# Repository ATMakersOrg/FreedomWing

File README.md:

# FreedomWing Joystick Adapter

## Overview

The FreedomWing Joystick Adapter provides a way to connect a powerchair joystick to a gaming system. This can enable someone to game with the same joystick they use to control their powerchair. This adapter is compatible with joysticks that attach to the powerchair via a DB9 connector. 

The FreedomWing was designed by [ATMakers](http://atmakers.org/) in collaboration with [The AbleGamers Charity](http://ablegamers.org/) and [GRA-V Robotics](https://www.facebook.com/grav.robotics/). [Makers Making Change](https://makersmakingchange.com/) updated the design of the PCB and created a basic set of documentation for FreedomWing 1.1.

This device is Open Source Hardware. Everything needed to build the device is contained within this repository.

More information is available at http://atmakers.org/featherwing

## License

Software is licensed under the MIT Open Source license.  A copy is provided in the 'software' subdirectory

Hardware designs are licensed under the Creative Commons Attribution Share Alike (CC-BY:SA) license.  A copy is provided in the 'hardware' subdirectory.

Documentation is licensed under the Creative Commons Attribution Share Alike (CC-BY:SA) license.  A copy is provided in the 'documentation' subdirectory.

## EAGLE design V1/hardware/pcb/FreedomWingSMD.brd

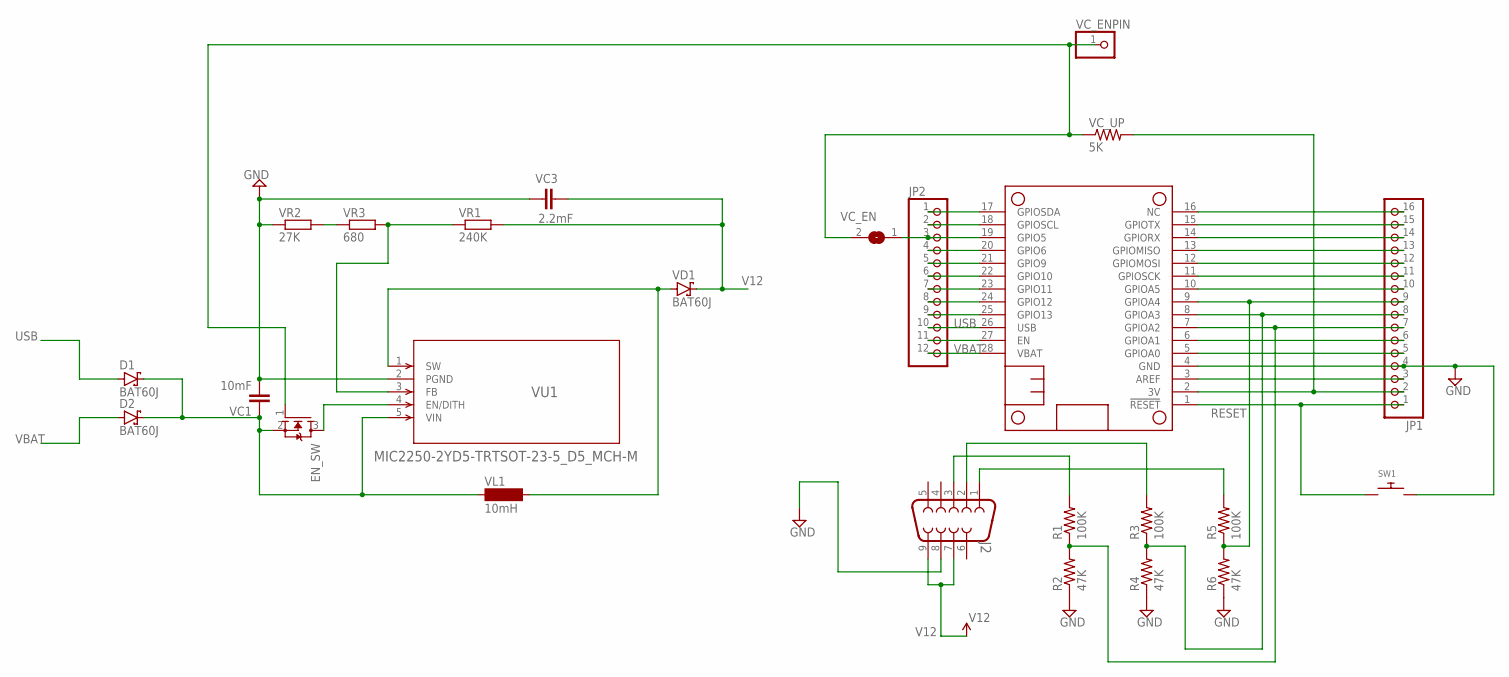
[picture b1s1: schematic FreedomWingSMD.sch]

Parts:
D1, D2: BAT60J; SOD323_ST
EN_SW: MOSFET-NREFLOW; SOT23
J2: DB9MALE; DB9_MALE
JP1: PINHD-1X16; 1X16
JP2: PINHD-1X12; 1X12
MS1: FEATHERWING_NODIM; FEATHERWING_DIM
R1, R3, R5: 100K; R0805
R2, R4, R6: 47K; R0805
SW1: SWITCH_PUSHBUTTONC&K_KSS; BTN_CK_KSS
VC1: 10mF; C0805
VC3: 2.2mF; C0805
VC_EN: SJW
VC_ENPIN: PINHD-1X1; 1X01
VC_UP: 5K; R0805
VD1: BAT60J; SOD323_ST
VL1: 10mH; MS50
VR1: 240K; R0805W
VR2: 27K; R0805W
VR3: 680; R0805W
VU1: MIC2250-2YD5-TRTSOT-23-5_D5_MCH-M; TSOT-23-5_D5_MCH-M

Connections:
3V: JP1.2, MS1.2 (3V), VC_UP.2
GND: J2.8, JP1.4, MS1.4 (GND), R2.1, R4.1, R6.1, SW1.P$2, VC1.2, VC3.1, VR2.1, VU1.2 (PGND)
unnamed: J2.3, R1.2
unnamed: JP2.1, MS1.17 (GPIOSDA)
unnamed: JP2.2, MS1.18 (GPIOSCL)
unnamed: JP2.3, MS1.19 (GPIO5), VC_EN.1
unnamed: JP1.7, MS1.7 (GPIOA2), R1.1, R2.2
unnamed: JP1.8, MS1.8 (GPIOA3), R3.1, R4.2
unnamed: JP1.9, MS1.9 (GPIOA4), R5.1, R6.2
unnamed: VR1.1, VR3.2, VU1.3 (FB)
unnamed: J2.2, R3.2
unnamed: J2.1, R5.2
unnamed: JP2.4, MS1.20 (GPIO6)
unnamed: JP2.5, MS1.21 (GPIO9)
unnamed: JP2.6, MS1.22 (GPIO10)
unnamed: JP2.7, MS1.23 (GPIO11)
unnamed: JP2.8, MS1.24 (GPIO12)
unnamed: JP2.9, MS1.25 (GPIO13)
unnamed: JP1.10, MS1.10 (GPIOA5)
unnamed: JP1.16, MS1.16 (NC)
unnamed: JP1.15, MS1.15 (GPIOTX)
unnamed: JP1.14, MS1.14 (GPIORX)
unnamed: JP1.13, MS1.13 (GPIOMISO)
unnamed: JP1.12, MS1.12 (GPIOMOSI)
unnamed: JP1.11, MS1.11 (GPIOSCK)
unnamed: JP2.11, MS1.27 (EN)
unnamed: EN_SW.3 (D), VU1.4 (EN/DITH)
unnamed: VD1.A, VL1.2, VU1.1 (SW)
unnamed: JP1.3, MS1.3 (AREF)
unnamed: EN_SW.1 (G), VC_EN.2, VC_ENPIN.1, VC_UP.1
unnamed: JP1.6, MS1.6 (GPIOA1)
unnamed: JP1.5, MS1.5 (GPIOA0)
unnamed: VR2.2, VR3.1
RESET: JP1.1, MS1.1 (!RESET), SW1.P$1
USB: D1.A, JP2.10, MS1.26 (USB)
V12: J2.7, J2.9, VC3.2, VD1.C, VR1.2
VBAT: D2.A, JP2.12, MS1.28 (VBAT)
VMAX: D1.C, D2.C, EN_SW.2 (S), VC1.1, VL1.1, VU1.5 (VIN)

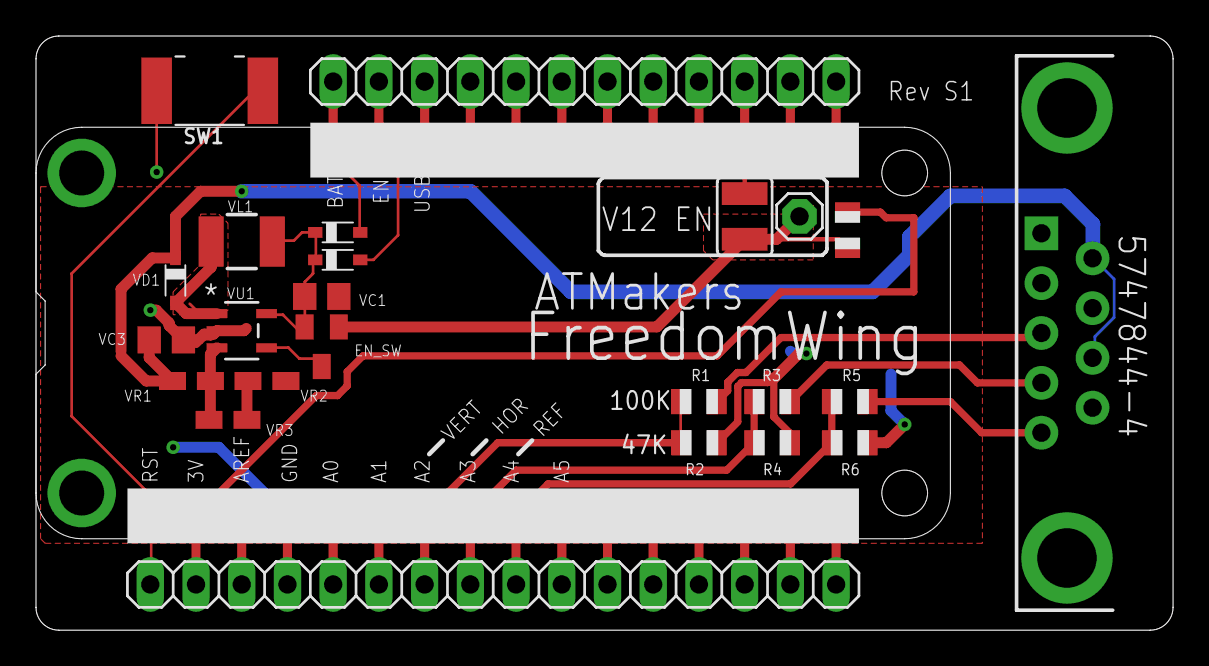
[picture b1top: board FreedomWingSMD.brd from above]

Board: 2 copper layers, 63.2 x 33.0 mm, 25 parts (0 on the bottom side), 38 nets.

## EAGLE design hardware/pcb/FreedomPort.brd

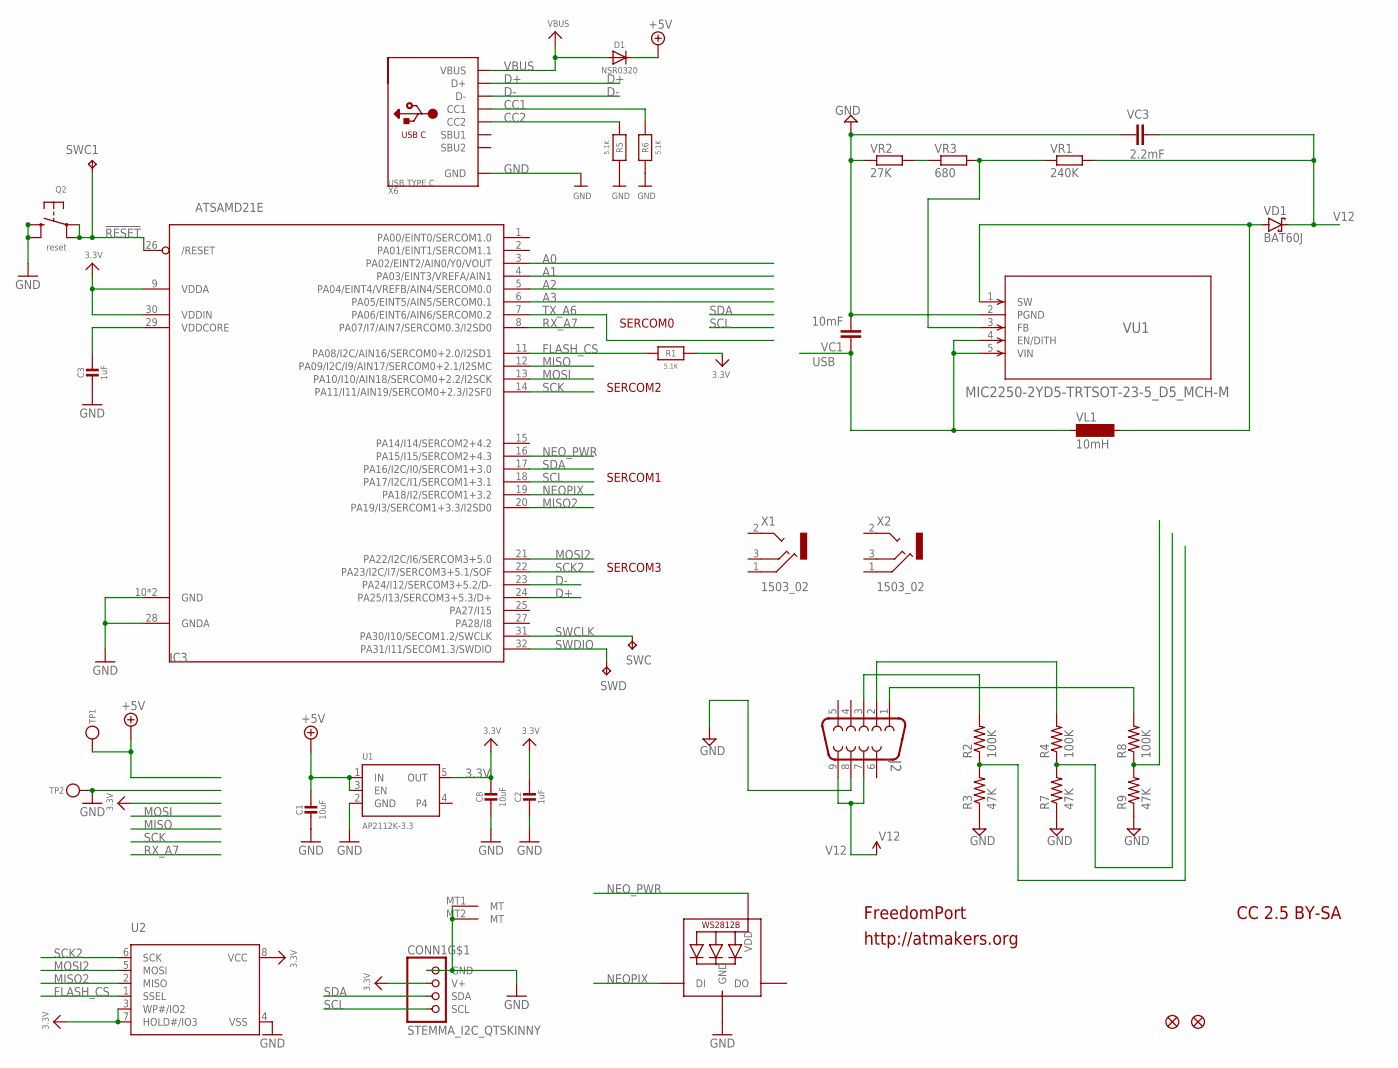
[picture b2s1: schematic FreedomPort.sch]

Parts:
C1, C8: 10uF; _0805MP
C2, C3: 1uF; _0402NO
CONN1: STEMMA_I2C_QTSKINNY; JST_SH4_SKINNY
D1: NSR0320; SOD-323_MINI
IC3: ATSAMD21E; QFN32_5MM
J2: DB9MALE; DB9_MALE
LED1: WS2812B_SK6805_1515; SK6805_1515
Q2: reset; BTN_KMR2_4.6X2.8
R1, R5, R6: 5.1K; _0402NO
R2, R4, R8: 100K; R0805
R3, R7, R9: 47K; R0805
SWC, SWC1: TPB1,27; B1,27
SWD: TPB1,27; B1,27
TP1, TP2: TESTPOINT_1X3; TESTPOINT_RECT_1X3MM
U1: AP2112K-3.3; SOT23-5
U2: SPIFLASH_8PIN; SOIC8_150MIL
U$6, U$8: FIDUCIAL_1MM
VC1: 10mF; C0805
VC3: 2.2mF; C0805
VD1: BAT60J; SOD323_ST
VL1: 10mH; MS50
VR1: 240K; R0805W
VR2: 27K; R0805W
VR3: 680; R0805W
VU1: MIC2250-2YD5-TRTSOT-23-5_D5_MCH-M; TSOT-23-5_D5_MCH-M
X1, X2: 1503_02
X6: USB TYPE C; USB_C_CUSB31-CFM2AX-01-X

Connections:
3.3V: C2.1, C8.1, CONN1.2 (V+), IC3.9 (VDDA), IC3.30 (VDDIN), R1.1, U1.5 (OUT), U2.3 (WP#/IO2), U2.7 (HOLD#/IO3), U2.8 (VCC)
!RESET: IC3.26 (/RESET), Q2.A, Q2.A' (P1), SWC1.TP
+5V: C1.1, D1.C, TP1.P$1, U1.1 (IN), U1.3 (EN)
A0: IC3.3 (PA02/EINT2/AIN0/Y0/VOUT)
A1: IC3.4 (PA03/EINT3/VREFA/AIN1)
A2: IC3.5 (PA04/EINT4/VREFB/AIN4/SERCOM0.0)
A3: IC3.6 (PA05/EINT5/AIN5/SERCOM0.1)
CC1: R6.2, X6.A5 (CC1)
CC2: R5.2, X6.B5 (CC2)
D+: IC3.24 (PA25/I13/SERCOM3+5.3/D+), X6.A6 (D+), X6.B6 (D+)
D-: IC3.23 (PA24/I12/SERCOM3+5.2/D-), X6.A7 (D-), X6.B7 (D-)
FLASH_CS: IC3.11 (PA08/I2C/AIN16/SERCOM0+2.0/I2SD1), R1.2, U2.1 (SSEL)
GND: C1.2, C2.2, C3.2, C8.2, CONN1.1 (GND), CONN1.MT1 (MT), CONN1.MT2 (MT), IC3.10 (GND), IC3.28 (GNDA), IC3.33 (GND), J2.8, LED1.4 (GND), Q2.B (S), Q2.B' (S1), R3.1, R5.1, R6.1, R7.1, R9.1, TP2.P$1, U1.2 (GND), U2.4 (VSS), VC1.2, VC3.1, VR2.1, VU1.2 (PGND), X6.A1B12 (GND), X6.B1A12 (GND)
MISO: IC3.12 (PA09/I2C/I9/AIN17/SERCOM0+2.1/I2SMC)
MISO2: IC3.20 (PA19/I3/SERCOM1+3.3/I2SD0), U2.2 (MISO)
MOSI: IC3.13 (PA10/I10/AIN18/SERCOM0+2.2/I2SCK)
MOSI2: IC3.21 (PA22/I2C/I6/SERCOM3+5.0), U2.5 (MOSI)
unnamed: J2.3, R2.2
unnamed: R2.1, R3.2
unnamed: R4.1, R7.2
unnamed: R8.1, R9.2
unnamed: VR1.1, VR3.2, VU1.3 (FB)
unnamed: J2.2, R4.2
unnamed: J2.1, R8.2
unnamed: VD1.A, VL1.2, VU1.1 (SW)
unnamed: VR2.2, VR3.1
NEOPIX: IC3.19 (PA18/I2/SERCOM1+3.2), LED1.1 (DI)
NEO_PWR: IC3.16 (PA15/I15/SERCOM2+4.3), LED1.2 (VDD)
RX_A7: IC3.8 (PA07/I7/AIN7/SERCOM0.3/I2SD0)
SCK: IC3.14 (PA11/I11/AIN19/SERCOM0+2.3/I2SF0)
SCK2: IC3.22 (PA23/I2C/I7/SERCOM3+5.1/SOF), U2.6 (SCK)
SCL: CONN1.4 (SCL), IC3.18 (PA17/I2C/I1/SERCOM1+3.1)
SDA: CONN1.3 (SDA), IC3.17 (PA16/I2C/I0/SERCOM1+3.0)
SWCLK: IC3.31 (PA30/I10/SECOM1.2/SWCLK), SWC.TP
SWDIO: IC3.32 (PA31/I11/SECOM1.3/SWDIO), SWD.TP
TX_A6: IC3.7 (PA06/EINT6/AIN6/SERCOM0.2)
USB: VC1.1, VL1.1, VU1.4 (EN/DITH), VU1.5 (VIN)
V12: J2.7, J2.9, VC3.2, VD1.C, VR1.2
VBUS: D1.A, X6.A4B9 (VBUS), X6.B4A9 (VBUS)
VDDCORE: C3.1, IC3.29 (VDDCORE)

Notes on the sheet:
FreedomPort
http://atmakers.org
CC 2.5 BY-SA
SERCOM0
SERCOM1
SERCOM2
SERCOM3

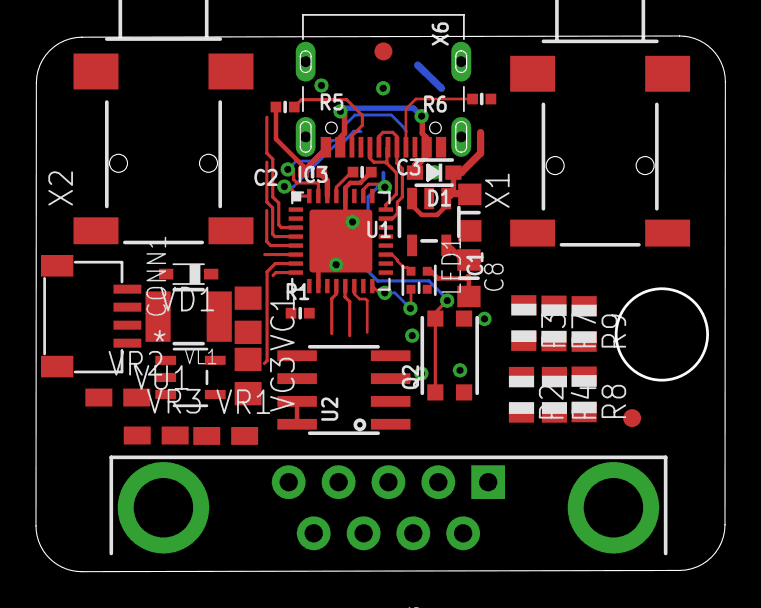
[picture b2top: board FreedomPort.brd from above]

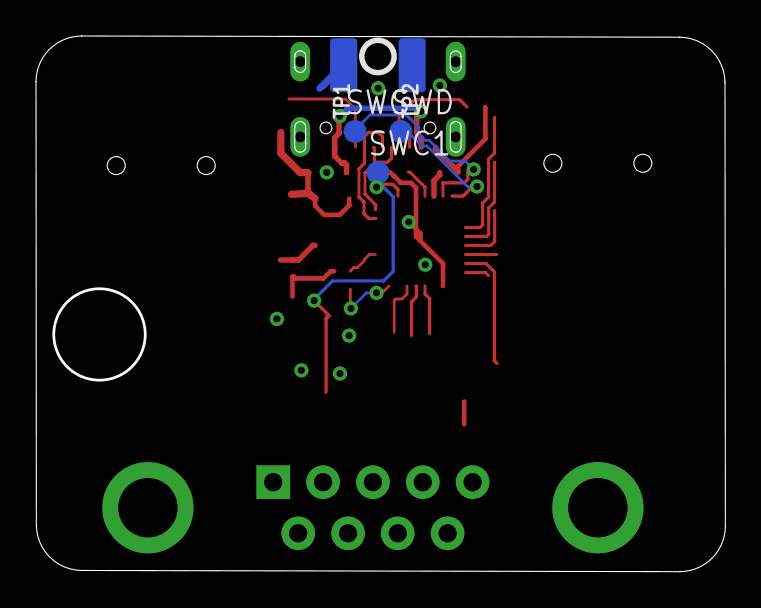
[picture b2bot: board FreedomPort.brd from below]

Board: 2 copper layers, 38.1 x 29.6 mm, 42 parts (7 on the bottom side), 31 nets.

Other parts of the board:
U$11: QTPY_BOT
U$12: PCBFEAT-REV-040
U$13: QTPY_TOP

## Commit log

2020-02-07 Initial Release
    This is not yet baked. And I am not certain that this should all be in one repository. However, it is a starting point and I want this in version control so we have a snapshot of what was actually us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
2020-02-07 Split hardware
    Also added the case files
2020-02-07 First changes after Launch
    Updated to add Schottky Diodes, Reset Switch & Jumper
2020-02-11 Adding Pix
2020-02-12 Adding Reset Tab
2021-02-17 Adding Initial SMD Version of the FreedomWing (Untested)
    Adding Initial SMD Version of the FreedomWing (Untested)
2021-02-18 Fixed schematic issues w/Voltage Regulator
2021-02-18 Added values and tweaked for 12V
2021-02-18 Switched to 2 layers & added stuff
2021-02-22 Adding Tester code
2021-02-22 Fixing name of readme
2021-02-22 Stupid git desktop
2021-02-22 Added a first pass at a standalone FreedomPort board
2022-12-22 FreedomWing 1.1 Update
    Added detailed documentation, photos, and updated PCB and enclosure files.
2022-12-22 Create FreedomWing.png
    Add render.
2022-12-22 Update changes to include documentation

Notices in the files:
parts and their libraries:
SparkFun-Connectors: Licensing: Creative Commons ShareAlike 4.0 International - https://creativecommons.org/licenses/by-sa/4.0
COPYRIGHT: Copyright (C) 2018 Accelerated Designs. All rights reserved
